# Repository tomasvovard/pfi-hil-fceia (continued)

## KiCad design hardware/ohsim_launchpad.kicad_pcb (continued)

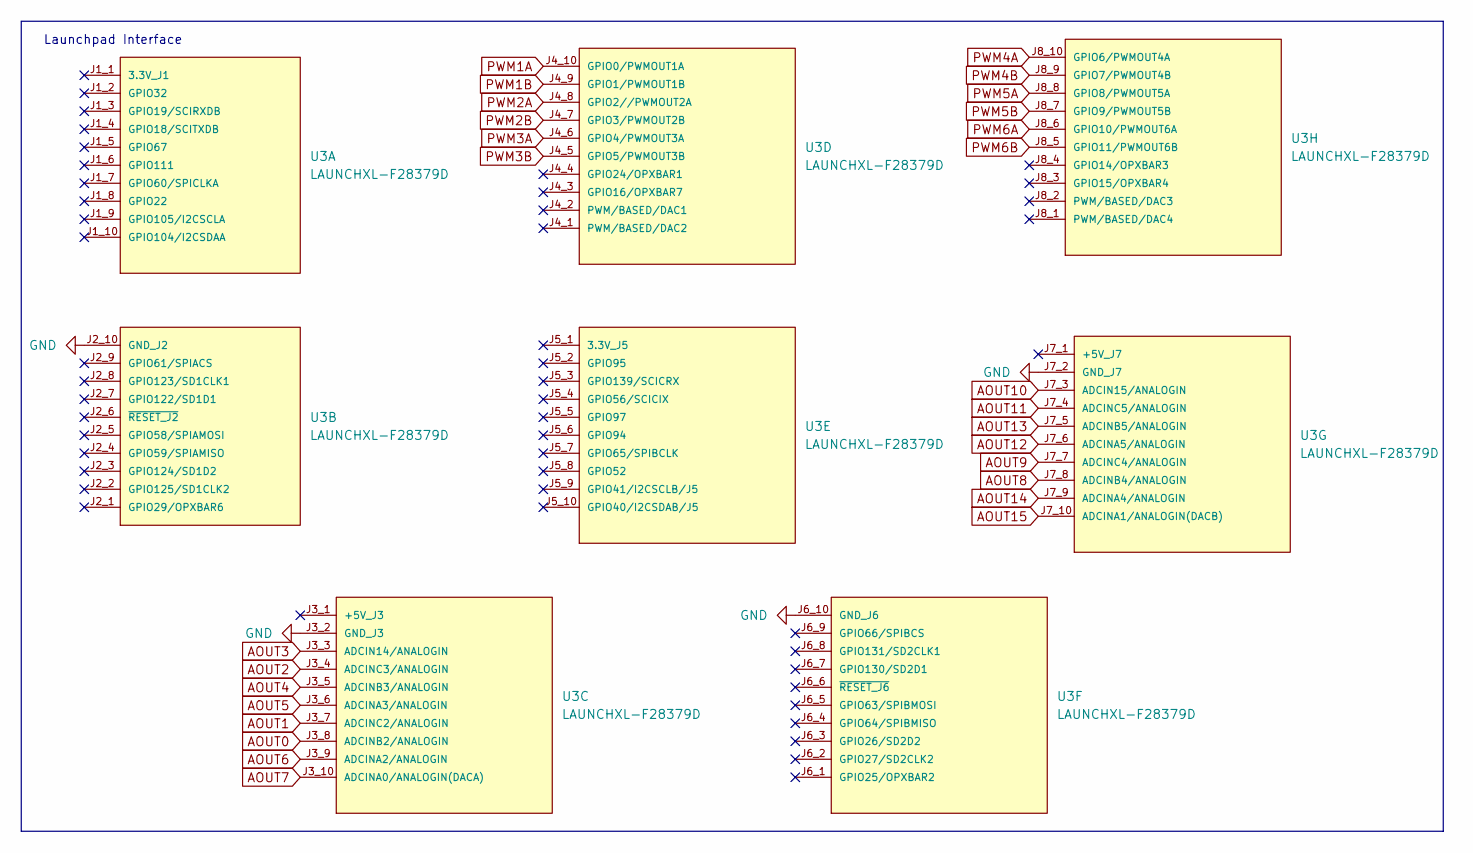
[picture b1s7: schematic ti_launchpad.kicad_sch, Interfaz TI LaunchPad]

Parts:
U3: LAUNCHXL-F28379D; MOD_LAUNCHXL-F28379D; PARTREV 2.0

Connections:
AOUT0: U3.J3_8 (ADCINB2/ANALOGIN); also elsewhere on the board
AOUT1: U3.J3_7 (ADCINC2/ANALOGIN); also elsewhere on the board
AOUT2: U3.J3_4 (ADCINC3/ANALOGIN); also elsewhere on the board
AOUT3: U3.J3_3 (ADCIN14/ANALOGIN); also elsewhere on the board
AOUT4: U3.J3_5 (ADCINB3/ANALOGIN); also elsewhere on the board
AOUT5: U3.J3_6 (ADCINA3/ANALOGIN); also elsewhere on the board
AOUT6: U3.J3_9 (ADCINA2/ANALOGIN); also elsewhere on the board
AOUT7: U3.J3_10 (ADCINA0/ANALOGIN(DACA)); also elsewhere on the board
AOUT8: U3.J7_8 (ADCINB4/ANALOGIN); also elsewhere on the board
AOUT9: U3.J7_7 (ADCINC4/ANALOGIN); also elsewhere on the board
AOUT10: U3.J7_3 (ADCIN15/ANALOGIN); also elsewhere on the board
AOUT11: U3.J7_4 (ADCINC5/ANALOGIN); also elsewhere on the board
AOUT12: U3.J7_6 (ADCINA5/ANALOGIN); also elsewhere on the board
AOUT13: U3.J7_5 (ADCINB5/ANALOGIN); also elsewhere on the board
AOUT14: U3.J7_9 (ADCINA4/ANALOGIN); also elsewhere on the board
AOUT15: U3.J7_10 (ADCINA1/ANALOGIN(DACB)); also elsewhere on the board
GND: U3.J2_10 (GND_J2), U3.J3_2 (GND_J3), U3.J6_10 (GND_J6), U3.J7_2 (GND_J7); also elsewhere on the board
PWM1A: U3.J4_10 (GPIO0/PWMOUT1A); also elsewhere on the board
PWM1B: U3.J4_9 (GPIO1/PWMOUT1B); also elsewhere on the board
PWM2A: U3.J4_8 (GPIO2//PWMOUT2A); also elsewhere on the board
PWM2B: U3.J4_7 (GPIO3/PWMOUT2B); also elsewhere on the board
PWM3A: U3.J4_6 (GPIO4/PWMOUT3A); also elsewhere on the board
PWM3B: U3.J4_5 (GPIO5/PWMOUT3B); also elsewhere on the board
PWM4A: U3.J8_10 (GPIO6/PWMOUT4A); also elsewhere on the board
PWM4B: U3.J8_9 (GPIO7/PWMOUT4B); also elsewhere on the board
PWM5A: U3.J8_8 (GPIO8/PWMOUT5A); also elsewhere on the board
PWM5B: U3.J8_7 (GPIO9/PWMOUT5B); also elsewhere on the board
PWM6A: U3.J8_6 (GPIO10/PWMOUT6A); also elsewhere on the board
PWM6B: U3.J8_5 (GPIO11/PWMOUT6B); also elsewhere on the board

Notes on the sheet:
Launchpad Interface

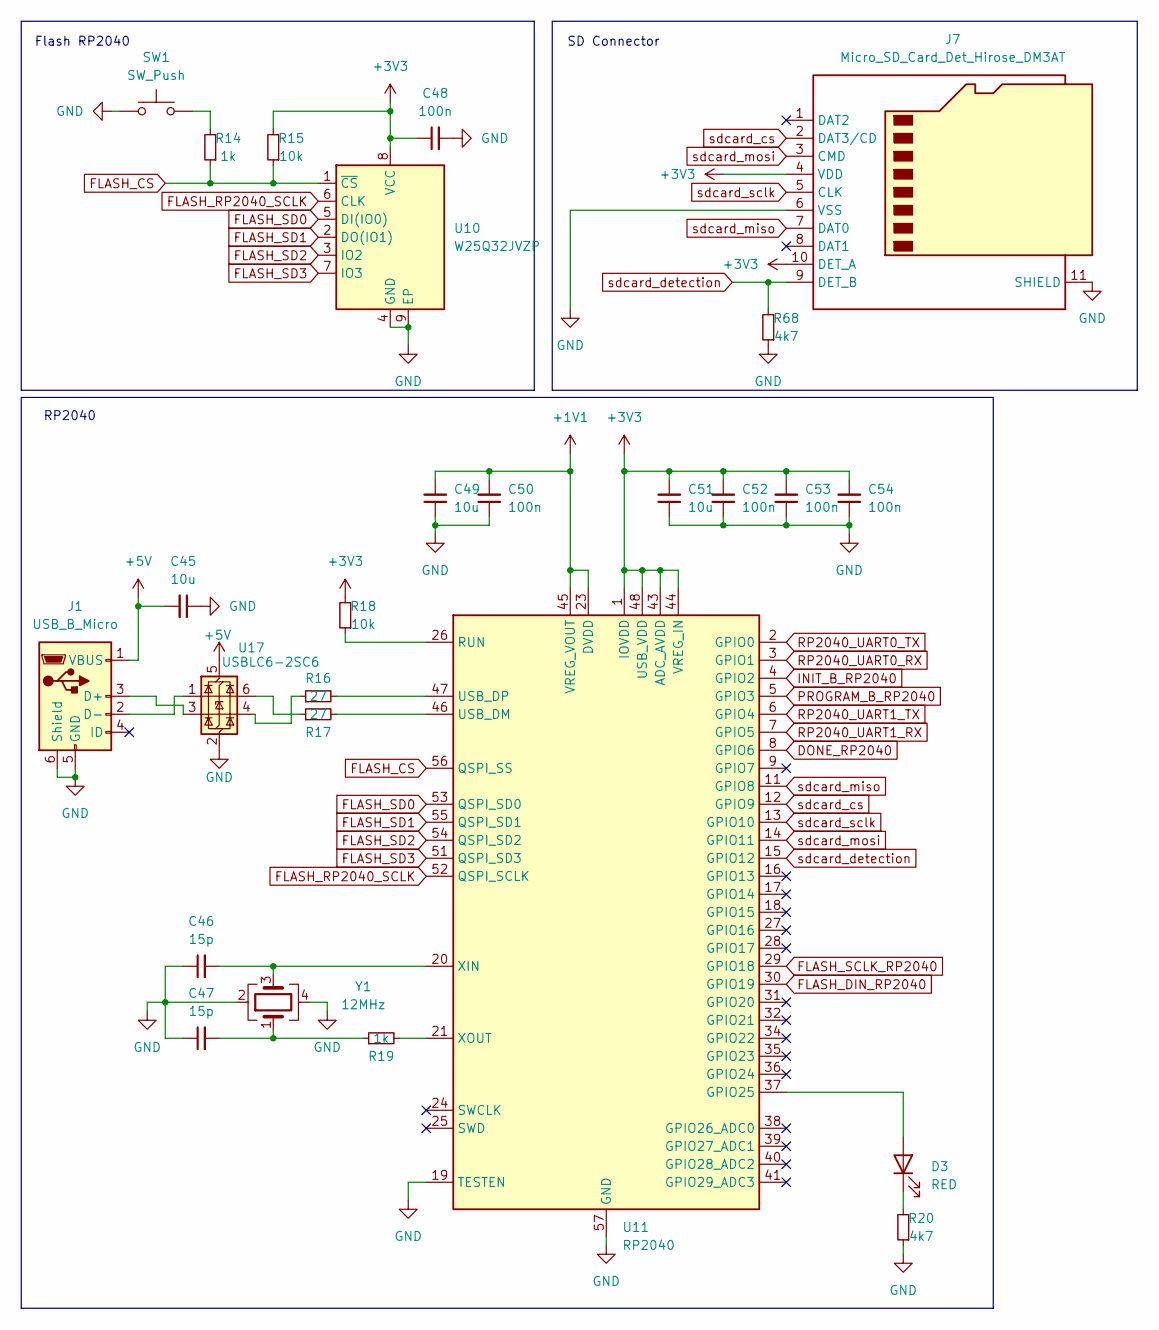
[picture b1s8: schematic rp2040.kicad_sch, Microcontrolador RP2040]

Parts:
C45, C49, C51: 10u; C_0805_2012Metric; JLCPCB C5137471
C46, C47: 15p; C_0805_2012Metric; JLCPCB C129642
C48, C50, C52, C53, C54: 100n; C_0603_1608Metric; JLCPCB C1591
D3: RED; LED_0603_1608Metric; JLCPCB C965799
J1: USB_B_Micro; USB_Micro-B_Amphenol_10118193-0001LF_Horizontal; JLCPCB Part # C132562
J7: Micro_SD_Card_Det_Hirose_DM3AT; microSD_HC_Hirose_DM3AT-SF-PEJM5; JLCPCB Part # C114218
R14, R19: 1k; R_0603_1608Metric; JLCPCB C2907002
R15, R18: 10k; R_0805_2012Metric; JLCPCB C115309
R16, R17: 27; R_0603_1608Metric; JLCPCB C25190
R20, R68: 4k7; R_0805_2012Metric; JLCPCB C6457904
SW1: SW_Push; SW_Push_SPST_NO_Alps_SKRK; JLCPCB Part # C115357
U10: W25Q32JVZP; WSON-8-1EP_6x5mm_P1.27mm_EP3.4x4.3mm; JLCPCB Part # C571260
U11: RP2040; QFN-56-1EP_7x7mm_P0.4mm_EP3.2x3.2mm; JLCPCB C2040
U17: USBLC6-2SC6; SOT-23-6; JLCPCB C7519
Y1: 12MHz; Crystal_SMD_3225-4Pin_3.2x2.5mm; JLCPCB Part # C524716

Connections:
+1V1: C49.2, C50.2, U11.23 (DVDD), U11.45 (VREG_VOUT), U11.50 (DVDD)
+3V3: C48.1, C51.2, C52.2, C53.2, C54.2, J7.4 (VDD), J7.10 (DET_A), R15.2, R18.2, U10.8 (VCC), U11.1 (IOVDD), U11.10 (IOVDD), U11.22 (IOVDD), U11.33 (IOVDD), U11.42 (IOVDD), U11.43 (ADC_AVDD), U11.44 (VREG_IN), U11.48 (USB_VDD), U11.49 (IOVDD); also elsewhere on the board
+5V: C45.2, J1.1 (VBUS), U17.5 (VBUS); also elsewhere on the board
DONE_RP2040: U11.8 (GPIO6); also elsewhere on the board
FLASH_CS: R14.1, R15.1, U10.1 (~CS), U11.56 (QSPI_SS)
FLASH_DIN_RP2040: U11.30 (GPIO19); also elsewhere on the board
FLASH_RP2040_SCLK: U10.6 (CLK), U11.52 (QSPI_SCLK)
FLASH_SCLK_RP2040: U11.29 (GPIO18); also elsewhere on the board
FLASH_SD0: U10.5 (DI(IO0)), U11.53 (QSPI_SD0)
FLASH_SD1: U10.2 (DO(IO1)), U11.55 (QSPI_SD1)
FLASH_SD2: U10.3 (IO2), U11.54 (QSPI_SD2)
FLASH_SD3: U10.7 (IO3), U11.51 (QSPI_SD3)
GND: C45.1, C46.1, C47.1, C48.2, C49.1, C50.1, C51.1, C52.1, C53.1, C54.1, J1.5 (GND), J1.6 (Shield), J7.6 (VSS), J7.11 (SHIELD), R20.1, R68.1, SW1.1, U10.4 (GND), U10.9 (EP), U11.19 (TESTEN), U11.57 (GND), U17.2 (GND), Y1.2, Y1.4; also elsewhere on the board
INIT_B_RP2040: U11.4 (GPIO2); also elsewhere on the board
unnamed: C47.2, R19.1, Y1.1
unnamed: D3.2 (A), U11.37 (GPIO25)
unnamed: D3.1 (K), R20.2
unnamed: J1.3 (D+), U17.3 (I/O2)
unnamed: J1.2 (D-), U17.1 (I/O1)
unnamed: R14.2, SW1.2
unnamed: R16.1, U17.4 (I/O2)
unnamed: R17.1, U17.6 (I/O1)
unnamed: R18.1, U11.26 (RUN)
unnamed: R17.2, U11.46 (USB_DM)
unnamed: R16.2, U11.47 (USB_DP)
unnamed: C46.2, U11.20 (XIN), Y1.3
unnamed: R19.2, U11.21 (XOUT)
PROGRAM_B_RP2040: U11.5 (GPIO3); also elsewhere on the board
RP2040_UART0_RX: U11.3 (GPIO1); also elsewhere on the board
RP2040_UART0_TX: U11.2 (GPIO0); also elsewhere on the board
RP2040_UART1_RX: U11.7 (GPIO5)
RP2040_UART1_TX: U11.6 (GPIO4)
sdcard_cs: J7.2 (DAT3/CD), U11.12 (GPIO9)
sdcard_detection: J7.9 (DET_B), R68.2, U11.15 (GPIO12)
sdcard_miso: J7.7 (DAT0), U11.11 (GPIO8)
sdcard_mosi: J7.3 (CMD), U11.14 (GPIO11)
sdcard_sclk: J7.5 (CLK), U11.13 (GPIO10)

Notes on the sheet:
SD Connector
Flash RP2040
RP2040

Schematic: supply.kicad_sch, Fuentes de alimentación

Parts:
C2, C3, C4, C10, C12, C14, C16, C19, C20, C22, C26: 4u7; C_0805_2012Metric; JLCPCB C98192
C5, C6, C7: 10u; C_0805_2012Metric; JLCPCB C5137471
C9, C15: 100u; C_1206_3216Metric; JLCPCB C268006
C11, C13, C17, C21, C31, C34, C35, C36, C38, C39, C41, C42, C43, C44: 0.47u; C_0402_1005Metric; JLCPCB C106255
D2: RED; LED_0603_1608Metric; JLCPCB C965799
L1, L2, L3: 2u2; IND_LQH3NPN2R2MMEL; JLCPCB C341775
R7: 10k; R_0805_2012Metric; JLCPCB C115309
R8: 100k; R_0603_1608Metric; JLCPCB C2906980
R9, R12: 22k; R_0603_1608Metric; JLCPCB C114065
R10: 240k; R_0603_1608Metric; JLCPCB C217899
R11: 120k; R_0603_1608Metric; JLCPCB C25808
R13: 33k; R_0603_1608Metric; JLCPCB C880143
U7, U8, U9: TLV62565DBVR; SOT-23-5; JLCPCB C87122

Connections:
+1V0: C7.1, C9.1, C15.1, C19.1, C22.1, C26.1, C36.1, C39.1, C42.1, C44.1, L3.2, R12.1; also elsewhere on the board
+1V8: C6.1, C14.1, C31.1, C34.1, L2.2, R10.1, U7.1 (EN); also elsewhere on the board
+3V3: C5.1, C10.1, C11.1, C12.1, C13.1, C16.1, C17.1, C20.1, C21.1, C35.1, C38.1, C41.1, C43.1, L1.2, R8.1; also elsewhere on the board
+5V: C2.1, C3.1, C4.1, R7.1, U7.4 (VIN), U8.1 (EN), U8.4 (VIN), U9.1 (EN), U9.4 (VIN); also elsewhere on the board
GND: C2.2, C3.2, C4.2, C5.2, C6.2, C7.2, C9.2, C10.2, C11.2, C12.2, C13.2, C14.2, C15.2, C16.2, C17.2, C19.2, C20.2, C21.2, C22.2, C26.2, C31.2, C34.2, C35.2, C36.2, C38.2, C39.2, C41.2, C42.2, C43.2, C44.2, D2.1 (K), R9.2, R11.2, R13.2, U7.2 (GND), U8.2 (GND), U9.2 (GND); also elsewhere on the board
unnamed: D2.2 (A), R7.2
unnamed: R8.2, R9.1, U7.5 (FB)
unnamed: L1.1, U7.3 (SW)
unnamed: R10.2, R11.1, U8.5 (FB)
unnamed: L2.1, U8.3 (SW)
unnamed: R12.2, R13.1, U9.5 (FB)
unnamed: L3.1, U9.3 (SW)

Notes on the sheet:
Supply 1.8V (VCCAUX)
Supply 3.3V (VCCO)
Power-On LED
Supply 1.0(VCCBRAM, VCCINT)
Vout = 0.6*(1+R1/R2)

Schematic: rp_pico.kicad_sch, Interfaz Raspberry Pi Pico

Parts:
U15: Pico; RPi_Pico_SMD_TH

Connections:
AOUT2: U15.32 (GPIO27_ADC1); also elsewhere on the board
AOUT3: U15.34 (GPIO28_ADC2); also elsewhere on the board
AOUT4: U15.31 (GPIO26_ADC0); also elsewhere on the board
GND: U15.3 (GND), U15.8 (GND), U15.13 (GND), U15.18 (GND), U15.23 (GND), U15.28 (GND), U15.33 (AGND), U15.38 (GND); also elsewhere on the board
PWM1A: U15.14 (GPIO10); also elsewhere on the board
PWM1B: U15.15 (GPIO11); also elsewhere on the board
PWM2A: U15.16 (GPIO12); also elsewhere on the board
PWM2B: U15.17 (GPIO13); also elsewhere on the board
PWM3A: U15.19 (GPIO14); also elsewhere on the board
PWM3B: U15.20 (GPIO15); also elsewhere on the board
PWM4A: U15.26 (GPIO20); also elsewhere on the board
PWM4B: U15.25 (GPIO19); also elsewhere on the board
PWM5A: U15.24 (GPIO18); also elsewhere on the board
PWM5B: U15.22 (GPIO17); also elsewhere on the board

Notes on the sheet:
RP Pico Interface

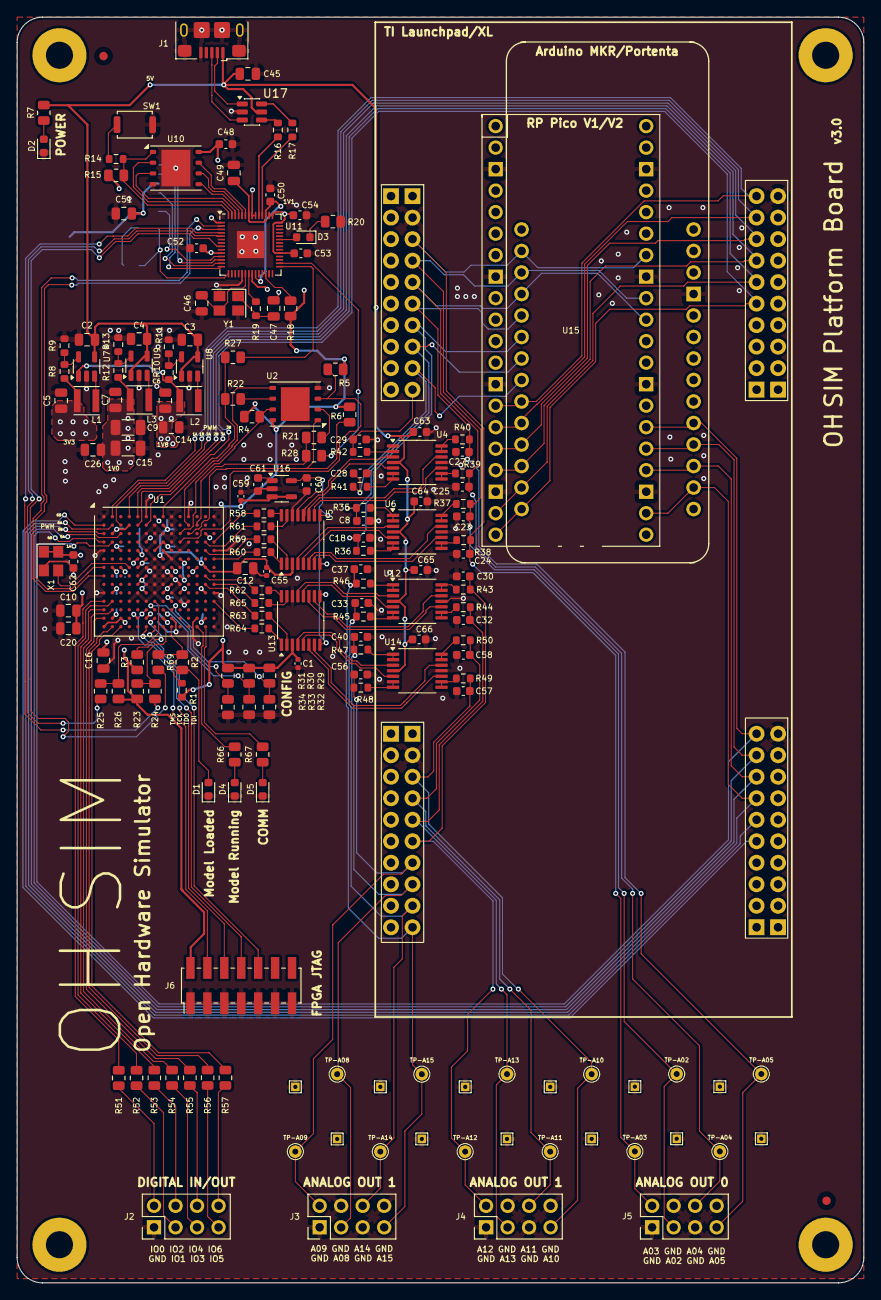
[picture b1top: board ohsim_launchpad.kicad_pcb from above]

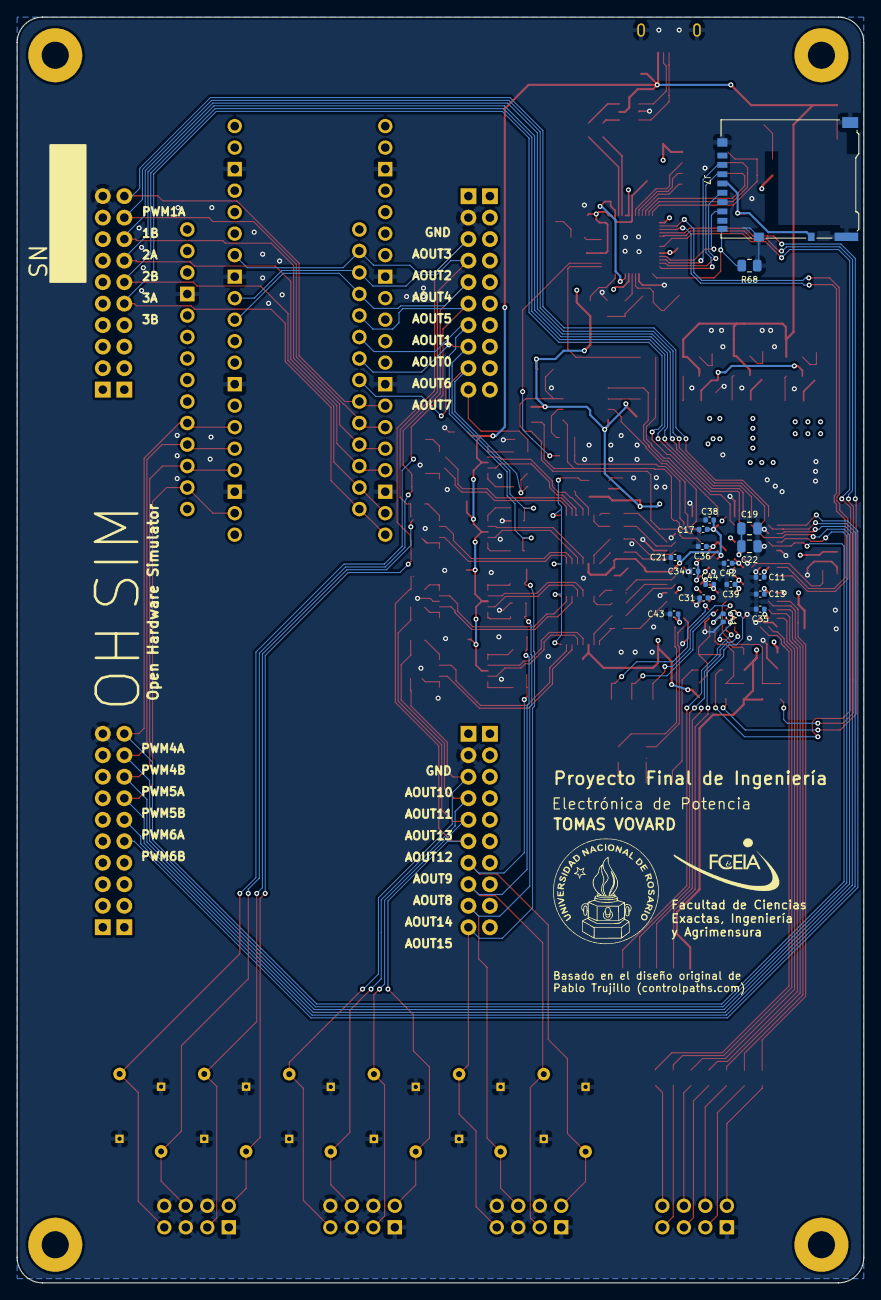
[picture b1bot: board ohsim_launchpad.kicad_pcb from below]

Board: 4 copper layers, 100.0 x 149.5 mm, 201 parts (18 on the bottom side), 161 nets.

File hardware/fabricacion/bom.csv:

Designator,Footprint,Quantity,Value,LCSC Part #
A1,Arduino_MKR_WiFi_1010_Socket,1,Arduino_MKR_WiFi_1010_Socket,
"C1, C11, C13, C17, C21, C31, C34, C35, C36, C38, C39, C41, C42, C43, C44, C55, C59",0402,17,0.47u,C106255
"C10, C12, C14, C16, C19, C2, C20, C22, C26, C3, C4",0805,11,4u7,C98192
"C15, C9",1206,2,100u,C268006
"C18, C23, C24, C25, C27, C28, C29, C30, C32, C33, C37, C40, C56, C57, C58, C8",0603,16,1n5,C96090
"C45, C49, C5, C51, C6, C7",0805,6,10u,C5137471
"C46, C47",0805,2,15p,C129642
"C48, C50, C52, C53, C54, C60, C61, C62, C63, C64, C65, C66",0603,12,100n,C1591
"D1, D4, D5",0603,3,BLUE,C89814
"D2, D3",0603,2,RED,C965799
J1,USB_Micro-B_Amphenol_10118193-0001LF_Horizontal,1,USB_B_Micro,C132562
"J2, J3, J4, J5",PinHeader_2x04_P2.54mm_Vertical,4,Conn_02x04_Odd_Even,
J6,PinHeader_2x07_P2.00mm_Vertical_SMD,1,Conn_02x07_Odd_Even,C19078805
J7,microSD_HC_Hirose_DM3AT-SF-PEJM5,1,Micro_SD_Card_Det_Hirose_DM3AT,C114218
"L1, L2, L3",IND_LQH3NPN2R2MMEL,3,2u2,C341775
R1,0603,1,330,C125768
R10,0603,1,240k,C217899
R11,0603,1,120k,C25808
"R12, R9",0603,2,22k,C114065
R13,0603,1,33k,C880143
"R14, R19, R35, R36, R37, R38, R39, R40, R41, R42, R43, R44, R45, R46, R47, R48, R49, R50",0603,18,1k,C2907002
"R15, R18, R7",0805,3,10k,C115309
"R16, R17, R58, R59, R60, R61, R62, R63, R64, R65",0603,10,27,C25190
"R2, R51, R52, R53, R54, R55, R56, R57",0805,8,100,C2907218
"R20, R23, R26, R29, R3, R30, R31, R32, R33, R34, R4, R5, R6, R66, R67, R68",0805,16,4k7,C6457904
"R21, R22, R24, R25, R27, R28, R69",0805,7,0,C2907215
R8,0603,1,100k,C2906980
SW1,SW_Push_SPST_NO_Alps_SKRK,1,SW_Push,C115357
"TP-A02, TP-A03, TP-A04, TP-A05, TP-A08, TP-A09, TP-A10, TP-A11, TP-A12, TP-A13, TP-A14, TP-A15",TestPoint_THTPad_D1.5mm_Drill0.7mm,12,TestPoint_signal,
"TP1, TP10, TP11, TP12, TP2, TP3, TP4, TP5, TP6, TP7, TP8, TP9",TestPoint_THTPad_1.0x1.0mm_Drill0.5mm,12,TestPoint_gnd,
U1,Xilinx_FTGB196,1,XC7S50-1FTGB196C,
U10,WSON-8-1EP_6x5mm_P1.27mm_EP3.4x4.3mm,1,W25Q32JVZP,C571260
U11,QFN-56-1EP_7x7mm_P0.4mm_EP3.2x3.2mm,1,RP2040,C2040
"U12, U14, U4, U6",TSSOP-14_4.4x5mm_P0.65mm,4,LMV324,C165067
"U13, U5",TSSOP-16_4.4x5mm_P0.65mm,2,AD53x8,C578186
U15,RPi_Pico_SMD_TH,1,Pico,
U16,SOT-23-5,1,REF2030,C528704
U17,SOT-23-6,1,USBLC6-2SC6,C7519
U2,WSON-8-1EP_6x5mm_P1.27mm_EP3.4x4mm,1,MX25L12833F,C2802709
U3,MOD_LAUNCHXL-F28379D,1,LAUNCHXL-F28379D,
"U7, U8, U9",SOT-23-5,3,TLV62565DBVR,C87122
X1,Crystal_SMD_3225-4Pin_3.2x2.5mm,1,SG-8018CE,C390488
Y1,Crystal_SMD_3225-4Pin_3.2x2.5mm,1,12MHz,C524716

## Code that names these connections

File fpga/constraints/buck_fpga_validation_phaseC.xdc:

# SPDX-License-Identifier: MIT
# Copyright (c) 2026 Tomás Vovard
# pfi-hil-fceia: OHSIM + modelo de buck (PFI Ingeniería Electrónica, FCEIA-UNR)

## buck_fpga_validation_phaseC.xdc
## Constraints para buck_fpga_validation_phaseC_top (Spartan-7
## xc7s50ftgb196-1, Platform Board OHSIM).
##
## IMPORTANTE: este archivo contiene SOLO constraints fisicos (pines,
## clock). NO tiene comandos de debug core (create_debug_core, etc.) --
## esos los agrega scripts/insert_ila.tcl DESPUES de la sintesis, y
## quedan volcados en el .xdc dentro de vivado_project/ al correr
## save_constraints (paso que ya hace el propio script). Si al abrir el
## proyecto generado ves esas lineas en el .xdc de adentro del proyecto,
## es esperado -- no las copies de vuelta a este archivo fuente, se
## regeneran solas cada vez que se corre insert_ila.tcl.

## ---------------------------------------------------------------------
## Clock del sistema: 30 MHz, 50% duty cycle
## ---------------------------------------------------------------------
set_property -dict {PACKAGE_PIN G4 IOSTANDARD LVCMOS33} [get_ports sys_clk]
create_clock -period 33.333 -name sys_clk_pin [get_ports sys_clk]

## ---------------------------------------------------------------------
## Tension del banco de configuracion 0 (DRC CFGBVS-1). Sin esto Vivado
## no puede determinar el soporte de I/O del banco 0 -- la placa usa
## 3.3V, VCCO como referencia (LVCMOS33 en todos los pines de este XDC).
## ---------------------------------------------------------------------
set_property CFGBVS VCCO [current_design]
set_property CONFIG_VOLTAGE 3.3 [current_design]

## ---------------------------------------------------------------------
## Entrada PWM
## ---------------------------------------------------------------------
set_property -dict {PACKAGE_PIN A2 IOSTANDARD LVCMOS33} [get_ports pwm_in]
set_false_path -from [get_ports pwm_in]

## ---------------------------------------------------------------------
## LEDs de estado
## ---------------------------------------------------------------------
set_property -dict {PACKAGE_PIN P12 IOSTANDARD LVCMOS33} [get_ports model_running_led]
set_property -dict {PACKAGE_PIN P13 IOSTANDARD LVCMOS33} [get_ports comm_led]

## ---------------------------------------------------------------------
## DAC0 (AD5328 U5)
## ---------------------------------------------------------------------
set_property -dict {PACKAGE_PIN D13 IOSTANDARD LVCMOS33} [get_ports dac0_din]
set_property -dict {PACKAGE_PIN F14 IOSTANDARD LVCMOS33} [get_ports dac0_ldac]
set_property -dict {PACKAGE_PIN E13 IOSTANDARD LVCMOS33} [get_ports dac0_sync]
set_property -dict {PACKAGE_PIN D14 IOSTANDARD LVCMOS33} [get_ports dac0_sclk]

## ---------------------------------------------------------------------
## DAC1 (AD5328 U13)
## ---------------------------------------------------------------------
set_property -dict {PACKAGE_PIN J14 IOSTANDARD LVCMOS33} [get_ports dac1_din]
set_property -dict {PACKAGE_PIN L14 IOSTANDARD LVCMOS33} [get_ports dac1_ldac]
set_property -dict {PACKAGE_PIN J13 IOSTANDARD LVCMOS33} [get_ports dac1_sync]
set_property -dict {PACKAGE_PIN H13 IOSTANDARD LVCMOS33} [get_ports dac1_sclk]

## ---------------------------------------------------------------------
## DIO 0-2: PWM/Vsw/Vx, salidas
## ---------------------------------------------------------------------
set_property -dict {PACKAGE_PIN L1 IOSTANDARD LVCMOS33} [get_ports dio_pwm_sync]
set_property -dict {PACKAGE_PIN L2 IOSTANDARD LVCMOS33} [get_ports dio_vsw]
set_property -dict {PACKAGE_PIN M1 IOSTANDARD LVCMOS33} [get_ports dio_vx]

## ---------------------------------------------------------------------
## Disparo del ensayo + seleccion de R (codigo Gray): DOS opciones de
## cableado, mutuamente excluyentes -- dejar UNA activa y la otra
## comentada segun cómo esté armado el banco en cada momento. Cambiar de
## opcion es edicion de este archivo nada mas, no toca el top ni el
## testbench (los 3 puertos logicos -- dio_trigger_in, dio_rsel_b0_in,
## dio_rsel_b1_in -- son los mismos en las dos opciones, el XDC es
## exactamente la capa que abstrae a qué pin fisico apuntan).
## ---------------------------------------------------------------------

## --- OPCION A (comentada): jumpers manuales a GND por el conector J2 ---
## Pines DIO del conector J2 (M2/N1/P2). Pull-UP: el conector J2 solo
## expone GND hacia afuera, asi que un jumper pasivo solo puede forzar un
## 0 -- con pull-up el reposo ya es 1 y el jumper es lo que efectivamente
## controla el pin (el disparo es "conectar y SACAR" el jumper).
# set_property -dict {PACKAGE_PIN M2 IOSTANDARD LVCMOS33} [get_ports dio_trigger_in]
# set_property -dict {PACKAGE_PIN N1 IOSTANDARD LVCMOS33} [get_ports dio_rsel_b0_in]
# set_property -dict {PACKAGE_PIN P2 IOSTANDARD LVCMOS33} [get_ports dio_rsel_b1_in]
# set_property PULLTYPE PULLUP [get_ports dio_trigger_in]
# set_property PULLTYPE PULLUP [get_ports dio_rsel_b0_in]
# set_property PULLTYPE PULLUP [get_ports dio_rsel_b1_in]

## --- OPCION B (ACTIVA): controlado por la Launchpad F28379D, por
## pines YA cableados a ella (PWM2A/PWM2B/PWM3A -- sobran, solo PWM1A se
## usa como pwm_in) -- evita el cable suelto de la Opcion A. Pull-DOWN,
## no pull-up: FPGA y Launchpad tienen fuentes independientes, comparten
## solo GND -- con pull-up, un GPIO de la Launchpad sin inicializar (o
## la placa apagada) recibiria 3.3V del propio riel de la FPGA por esa
## linea, "retroalimentando" un dominio de alimentacion ajeno. Pull-down
## solo referencia GND, que las dos placas comparten siempre, esten o no
## alimentadas -- no hay ruta para que una empuje corriente al riel de
## la otra. Con esto el reposo pasa a ser 0 (no 1): la Launchpad
## simplemente mantiene el pin en 0 y pulsa a 1, sin la vuelta de
## "conectar y soltar" que hacia falta con el jumper pasivo de la Opcion A.
set_property -dict {PACKAGE_PIN A4 IOSTANDARD LVCMOS33} [get_ports dio_trigger_in]  ; # PWM2A
set_property -dict {PACKAGE_PIN A5 IOSTANDARD LVCMOS33} [get_ports dio_rsel_b0_in]  ; # PWM2B
set_property -dict {PACKAGE_PIN B5 IOSTANDARD LVCMOS33} [get_ports dio_rsel_b1_in]  ; # PWM3A
set_property PULLTYPE PULLDOWN [get_ports dio_trigger_in]
set_property PULLTYPE PULLDOWN [get_ports dio_rsel_b0_in]
set_property PULLTYPE PULLDOWN [get_ports dio_rsel_b1_in]

## Comun a las dos opciones: asincronos respecto de sys_clk (van directo
## a sync_2ff.v adentro del top), false_path desde el pin de entrada por
## el mismo motivo que pwm_in.
set_false_path -from [get_ports dio_trigger_in]
set_false_path -from [get_ports dio_rsel_b0_in]
set_false_path -from [get_ports dio_rsel_b1_in]
